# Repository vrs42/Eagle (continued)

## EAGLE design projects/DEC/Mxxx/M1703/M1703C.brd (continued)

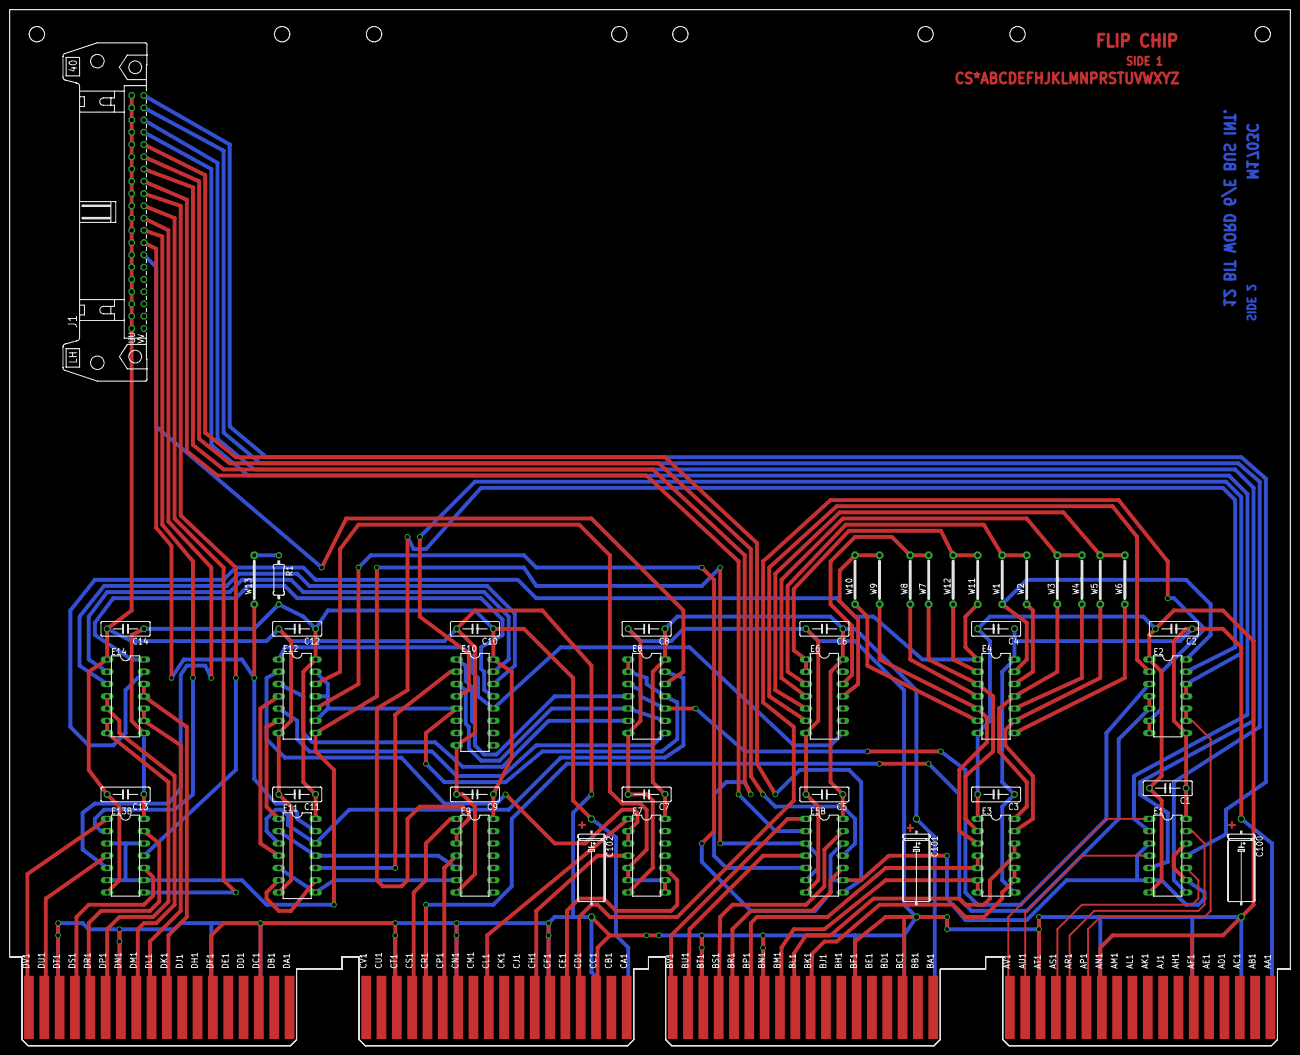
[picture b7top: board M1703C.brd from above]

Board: 2 copper layers, 265.3 x 214.6 mm, 49 parts (0 on the bottom side), 87 nets.

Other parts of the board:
U$3: FLIPCHIP
